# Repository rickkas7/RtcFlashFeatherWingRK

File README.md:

# RTC Flash FeatherWing

*MCP79410 RTC, SPI NOR flash, and Grove connector FeatherWing*

You typically insert this FeatherWing in a [Adafruit FeatherWing Doubler](https://www.adafruit.com/product/2890) or [Tripler](https://www.adafruit.com/product/3417) along with your device. It also works in the Particle Ethernet FeatherWing.

One of the limitations of the Gen 3 (nRF52) hardware is that it cannot wake up from SLEEP\_MODE\_DEEP based on time. That's because the nRF52 real-time-counter does not run in standby sleep mode. Also, when you wake up from SLEEP\_MODE\_DEEP, the Time object is not set until it's synchronized from the cloud again.

My solution to this is a simple Adafruit FeatherWing board with a MCP79410 real-time clock chip. It's inexpensive ($0.93 in single quantities) and tiny. 

Since I had so much room left on the FeatherWing, I also added:

- A CR1220 battery to power the chip with all external power removed (optional)
- 3 Grove expansion connectors (1 digital, 1 analog, 1 I2C, optional)
- A SPI NOR flash memory chip (optional)

## Using RTC to wake from SLEEP\_MODE\_DEEP

Here's a simple program to wake from SLEEP\_MODE\_DEEP:

```
#include "MCP79410RK.h"

SerialLogHandler logHandler;

MCP79410 rtc;

void setup() {
	// Make sure you call rtc.setup() from setup!
	rtc.setup();
}

void loop() {
	// Make sure you call rtc.loop() from loop!
	rtc.loop();

	// Wait 20 seconds after boot to try sleep
	if (millis() > 20000) {
		if (rtc.setAlarm(10)) {
			Log.info("About to SLEEP_MODE_DEEP for 10 seconds");
			System.sleep(SLEEP_MODE_DEEP);
		}
		else {
			Log.info("Failed to setAlarm, not sleeping");
			delay(10000);
		}
	}
}
```

For Gen 2 devices, you might do something like:

```
System.sleep(SLEEP_MODE_DEEP, 10);
```

but using the RTC it would be:

```
if (rtc.setAlarm(10)) {
    System.sleep(SLEEP_MODE_DEEP);
}
```

The reason for the error check around setAlarm is that the alarm can only be set after the RTC has been set to the correct time. Upon cold boot (no 3V3, no battery) the RTC won't be set and sleep cannot be used until the first clock synchronization. This is true even when delaying by seconds.

## Eagle Files

In the eagle directory are:

- FeatherRTC.sch and FeatherRTC.brd, the EagleCAD files
- FeatherRTC.lbr a library containing all of the parts on this board
- FeatherRTC.pdf, the schematic in pdf format

## MCP79410

The [MCP79410](https://github.com/rickkas7/MCP79410RK) library is used for the real-time clock (RTC) chip, and also to access the SRAM and EEPROM features.

There is extensive documentation in that Github for using it. You can find the full browsable API docs [here](http://rickkas7.github.io/MCP79410RK/class_m_c_p79410.html).

## SPI Flash

You can use a variety of SPI NOR flash chips:

- Winbond, such as a [W25Q32](https://www.digikey.com/product-detail/en/winbond-electronics/W25Q32JVSSIQ/W25Q32JVSSIQ-ND/5803981).
- Macronix, such as the [MX25L8006EM1I-12G](https://www.digikey.com/product-detail/en/macronix/MX25L8006EM1I-12G/1092-1117-ND/2744800)
- ISSI, such as a [IS25LQ080B](http://www.digikey.com/product-detail/en/issi-integrated-silicon-solution-inc/IS25LQ080B-JNLE/706-1331-ND/5189766).

The SPI chip select (CS) is connected to pin A5.

I recommend the [SpiFlashRK](https://github.com/rickkas7/SpiFlashRK) to access the flash memory at block level and [SpiffsParticleRK](https://github.com/rickkas7/SpiffsParticleRK) library for using the flash as a file system. 

Using a Winbond flash chip with SpiFlashRK, you'd declare an object like:

```
SpiFlashWinbond spiFlash(SPI, A5);
```

## BOM (Bill of Materials)

| Quantity | Item | Example |
| --- | --- | --- |
| 2 | 14 pf capacitor 0603| [Samsung CL10C140JB8NNNC](https://www.digikey.com/product-detail/en/samsung-electro-mechanics/CL10C140JB8NNNC/1276-2187-1-ND/3890273) |
| 1 | 2.2K resistor 0805 | [Panasonic ERJ-6GEYJ222V](https://www.digikey.com/product-detail/en/panasonic-electronic-components/ERJ-6GEYJ222V/P2.2KACT-ND/93214) |
| 2 | 10K resistor 0603 | [Panasonic ERJ-PA3J103V](https://www.digikey.com/product-detail/en/panasonic-electronic-components/ERJ-PA3J103V/P10KBZCT-ND/5036237)| 
| 1 | 32.768 kHz crystal 9pF | [EPSON FC-135](https://www.digikey.com/product-detail/en/epson/FC-135-32.7680KA-AC0/SER4084CT-ND/6132704) |
| 1 | MCP79410 RTC | [MCP79410-I/SN](https://www.digikey.com/product-detail/en/microchip-technology/MCP79410-I-SN/MCP79410-I-SN-ND/2480419) |
| 1 | SPI NOR flash memory | [Winbond W25Q32JV](https://www.digikey.com/product-detail/en/winbond-electronics/W25Q32JVSSIQ/W25Q32JVSSIQ-ND/5803981) | 
| 3 | Grove connector PTH vertical | [Seeed](https://www.digikey.com/product-detail/en/seeed-technology-co-ltd/110990030/1597-1082-ND/5482560) |
| 1 | CR1220 battery holder | [Keystone 1056TR](https://www.digikey.com/product-detail/en/keystone-electronics/1056/36-1056-ND/2020198) |
| | Male header pins 0.1" | [Sullins PRPC040SAAN-RC](https://www.digikey.com/product-detail/en/PRPC040SAAN-RC/S1011EC-40-ND/2775214) |

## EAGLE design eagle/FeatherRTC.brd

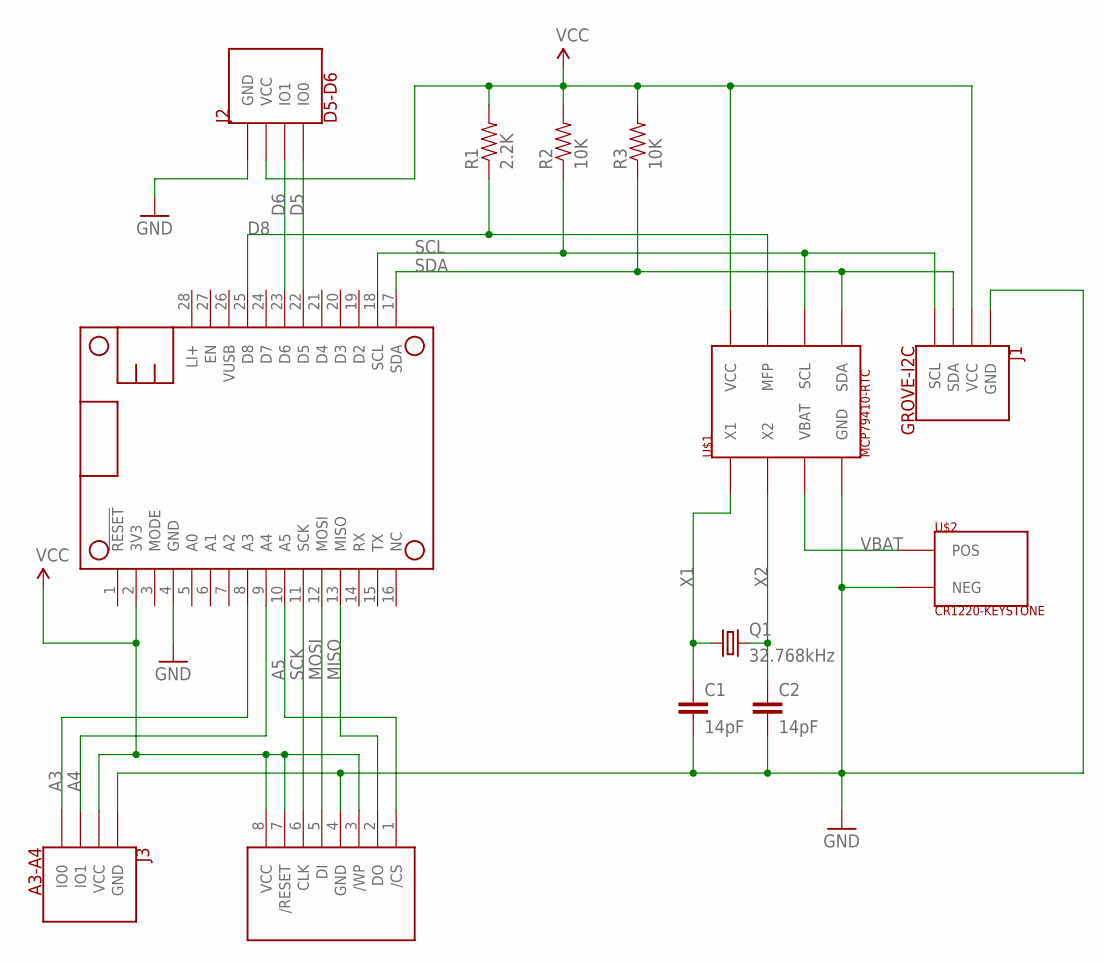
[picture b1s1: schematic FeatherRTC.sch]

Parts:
C1, C2: 14pF; 0603-CAP
J1: GROVE-I2C; GROVE-VERT-PTH
J2: D5-D6; GROVE-VERT-PTH
J3: A3-A4; GROVE-VERT-PTH
MS1: FEATHERWING_NODIM
Q1: 32.768kHz; FC-135
R1: 2.2K; 0805
R2, R3: 10K; 0603-RES
U$1: MCP79410-RTC; 8-SOIC-MICROCHIP-3.9
U$2: CR1220-KEYSTONE
U$3: W25Q-FLASH; 8-SOIC-WINBOND-208

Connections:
A3: J3.1 (IO0), MS1.8 (A3)
A4: J3.2 (IO1), MS1.9 (A4)
A5: MS1.10 (A5), U$3.1 (/CS)
D5: J2.1 (IO0), MS1.22 (D5)
D6: J2.2 (IO1), MS1.23 (D6)
D8: MS1.25 (D8), R1.1, U$1.7 (MFP)
GND: C1.2, C2.2, J1.4 (GND), J2.4 (GND), J3.4 (GND), MS1.4 (GND), U$1.4 (GND), U$2.NEG, U$3.4 (GND)
MISO: MS1.13 (MISO), U$3.2 (DO)
MOSI: MS1.12 (MOSI), U$3.5 (DI)
SCK: MS1.11 (SCK), U$3.6 (CLK)
SCL: J1.1 (SCL), MS1.18 (SCL), R2.1, U$1.6 (SCL)
SDA: J1.2 (SDA), MS1.17 (SDA), R3.1, U$1.5 (SDA)
VBAT: U$1.3 (VBAT), U$2.POS
VCC: J1.3 (VCC), J2.3 (VCC), J3.3 (VCC), MS1.2 (3V3), R1.2, R2.2, R3.2, U$1.8 (VCC), U$3.3 (/WP), U$3.7 (/RESET), U$3.8 (VCC)
X1: C1.1, Q1.1, U$1.1 (X1)
X2: C2.1, Q1.2, U$1.2 (X2)

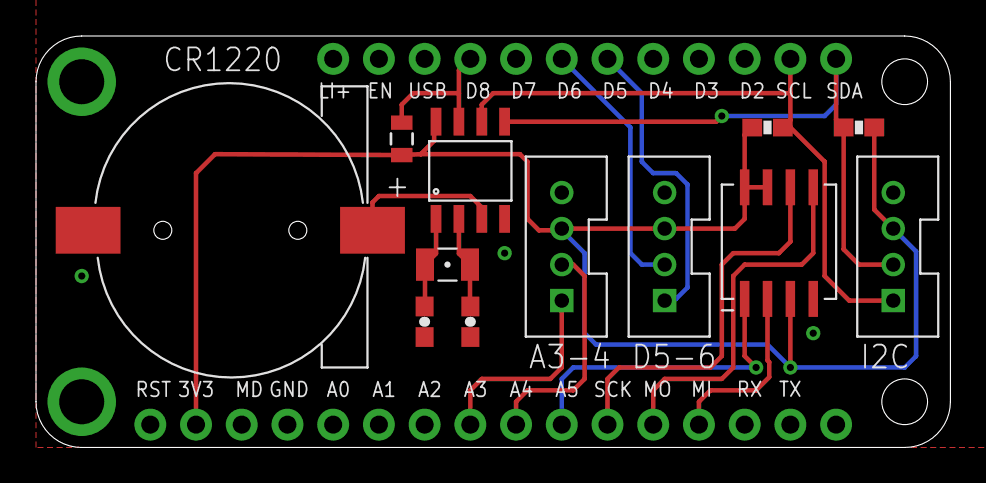
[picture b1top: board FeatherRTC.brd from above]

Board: 2 copper layers, 50.8 x 22.9 mm, 13 parts (0 on the bottom side), 16 nets.

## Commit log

2019-03-02 Initial checkin
